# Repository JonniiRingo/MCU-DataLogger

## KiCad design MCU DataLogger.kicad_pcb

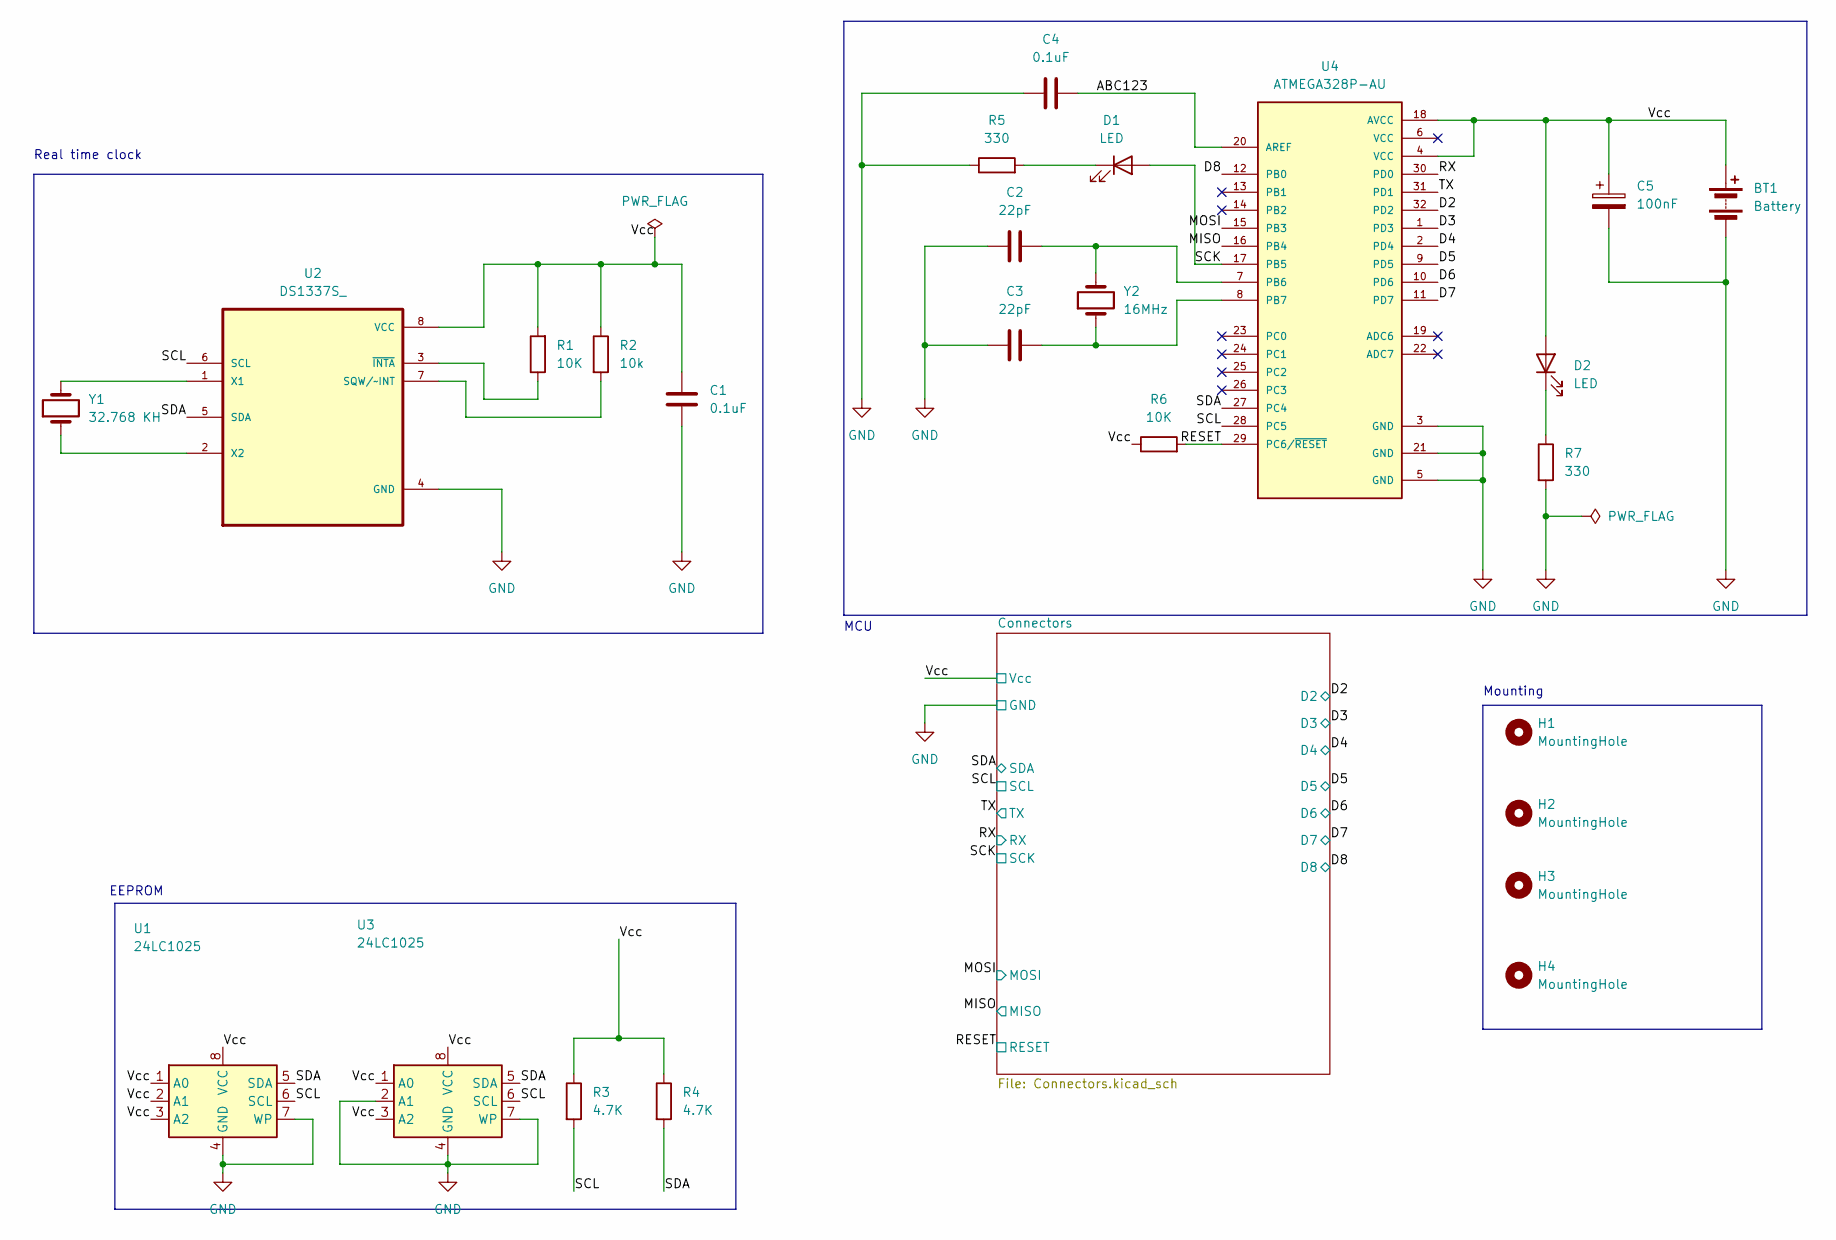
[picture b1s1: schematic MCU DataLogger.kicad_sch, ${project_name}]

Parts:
BT1: Battery; PinHeader_1x02_P2.54mm_Vertical
C1, C4: 0.1uF; C_0805_2012Metric
C2, C3: 22pF; C_0805_2012Metric
C5: 100nF; C_0805_2012Metric
D1, D2: LED; LED_0805_2012Metric
H1, H2, H3, H4: MountingHole; MountingHole_2.1mm
R1, R6: 10K; R_0805_2012Metric
R2: 10k; R_0805_2012Metric
R3, R4: 4.7K; R_0805_2012Metric
R5, R7: 330; R_0805_2012Metric
U1, U3: 24LC1025; SOIC-8_5.3x5.3mm_P1.27mm
U2: DS1337S_; SOIC127P600X175-8N
U4: ATMEGA328P-AU; QFP80P900X900X120-32N; PARTREV 8271A
Y1: 32.768 KH; Crystal_SMD_5032-2Pin_5.0x3.2mm
Y2: 16MHz; Crystal_SMD_5032-2Pin_5.0x3.2mm_HandSoldering

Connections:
/ABC123: C4.2, U4.20 (AREF)
/D2: U4.32 (PD2); also elsewhere on the board
/D3: U4.1 (PD3); also elsewhere on the board
/D4: U4.2 (PD4); also elsewhere on the board
/D5: U4.9 (PD5); also elsewhere on the board
/D6: U4.10 (PD6); also elsewhere on the board
/D7: U4.11 (PD7); also elsewhere on the board
/D8: U4.12 (PB0); also elsewhere on the board
/MISO: U4.16 (PB4); also elsewhere on the board
/MOSI: U4.15 (PB3); also elsewhere on the board
/RESET: R6.2, U4.29 (PC6/~RESET); also elsewhere on the board
/RX: U4.30 (PD0); also elsewhere on the board
/SCK: D1.2 (A), U4.17 (PB5); also elsewhere on the board
/SCL: R3.2, U1.6 (SCL), U2.6 (SCL), U3.6 (SCL), U4.28 (PC5); also elsewhere on the board
/SDA: R4.2, U1.5 (SDA), U2.5 (SDA), U3.5 (SDA), U4.27 (PC4); also elsewhere on the board
/TX: U4.31 (PD1); also elsewhere on the board
/Vcc: BT1.1 (+), C1.2, C5.1, D2.2 (A), R1.2, R2.1, R3.1, R4.1, R6.1, U1.1 (A0), U1.2 (A1), U1.3 (A2), U1.8 (VCC), U2.8 (VCC), U3.1 (A0), U3.3 (A2), U3.8 (VCC), U4.4 (VCC), U4.18 (AVCC); also elsewhere on the board
GND: BT1.2 (-), C1.1, C2.1, C3.1, C4.1, C5.2, R5.1, R7.2, U1.4 (GND), U1.7 (WP), U2.4 (GND), U3.2 (A1), U3.4 (GND), U3.7 (WP), U4.3 (GND), U4.5 (GND), U4.21 (GND); also elsewhere on the board
unnamed: D1.1 (K), R5.2
unnamed: D2.1 (K), R7.1
unnamed: R2.2, U2.7 (SQW/~INT)
unnamed: U2.1 (X1), Y1.2
unnamed: U2.2 (X2), Y1.1
unnamed: R1.1, U2.3 (~INTA)
unnamed: C2.2, U4.7 (PB6), Y2.2
unnamed: C3.2, U4.8 (PB7), Y2.1

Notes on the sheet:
Real time clock
Mounting
MCU
EEPROM

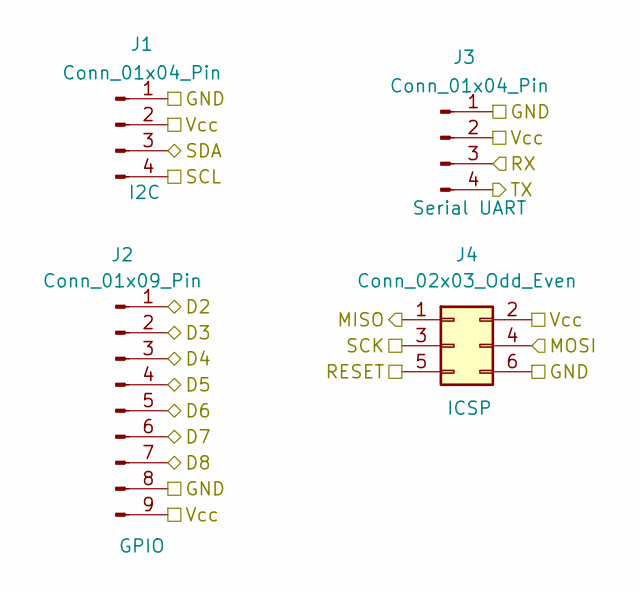
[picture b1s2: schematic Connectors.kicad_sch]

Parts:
J1, J3: Conn_01x04_Pin; PinHeader_1x04_P2.54mm_Vertical
J2: Conn_01x09_Pin; PinHeader_1x09_P2.54mm_Vertical
J4: Conn_02x03_Odd_Even; PinHeader_2x03_P2.54mm_Vertical

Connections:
/D2: J2.1; also elsewhere on the board
/D3: J2.2; also elsewhere on the board
/D4: J2.3; also elsewhere on the board
/D5: J2.4; also elsewhere on the board
/D6: J2.5; also elsewhere on the board
/D7: J2.6; also elsewhere on the board
/D8: J2.7; also elsewhere on the board
/MISO: J4.1; also elsewhere on the board
/MOSI: J4.4; also elsewhere on the board
/RESET: J4.5; also elsewhere on the board
/RX: J3.3; also elsewhere on the board
/SCK: J4.3; also elsewhere on the board
/SCL: J1.4; also elsewhere on the board
/SDA: J1.3; also elsewhere on the board
/TX: J3.4; also elsewhere on the board
/Vcc: J1.2, J2.9, J3.2, J4.2; also elsewhere on the board
GND: J1.1, J2.8, J3.1, J4.6; also elsewhere on the board

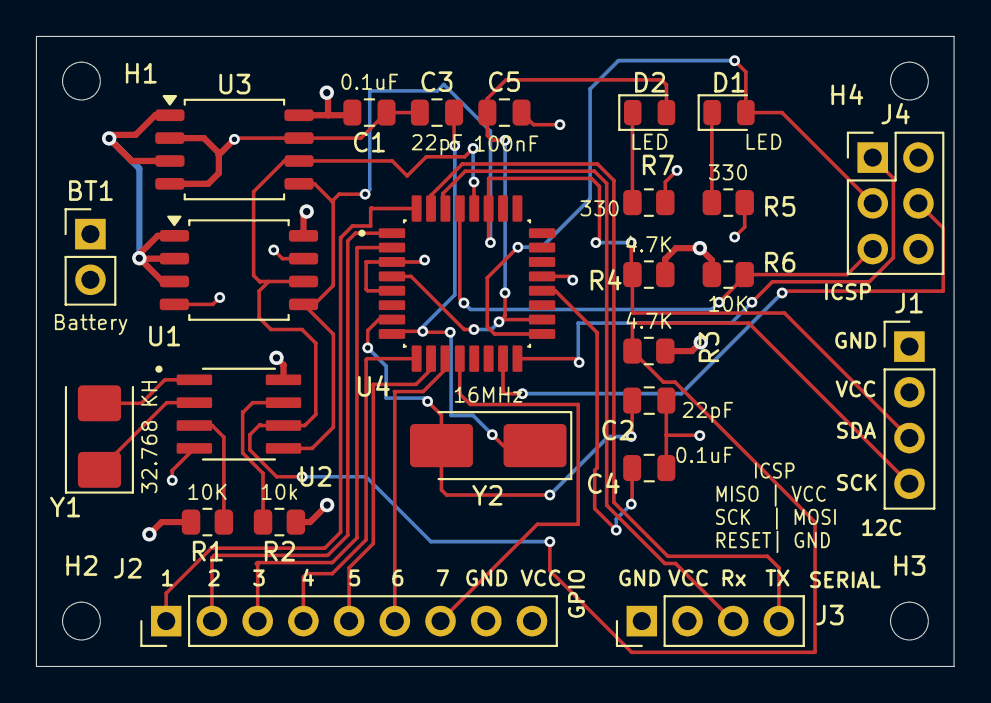
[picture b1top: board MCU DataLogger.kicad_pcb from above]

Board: 4 copper layers, 51.0 x 35.0 mm, 29 parts (0 on the bottom side), 26 nets.

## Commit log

2026-05-12 Settings selected and saved
2026-05-12 Symbols added to first and second sheet
2026-05-12 Symbols arranged pre annonation
2026-05-12 Symbols annotated with componenet values
2026-05-12 Added footprints to most of the symbols
2026-05-12 Sheet one wired
2026-05-12 Both sheets wired but Vcc in sheet 2 is not connected. Maybe some issue with Kicad mismatch
2026-05-13 Trying to resolve unconnected vcc
2026-05-13 Fixed the Erc pin not connected caused by capitalization error VCC vs Vcc
2026-05-13 Added netclass assignments
2026-05-13 Completed the comments on the schematic sheet
2026-05-13 Set up of new pcb with imported netlist
2026-05-13 Added the footprint to U1 and U2, staging for pcb schematic import and layout
2026-05-13 Completed the laout of the footprints in the pcb layer
2026-05-14 Resolved all the unconnected erc errors and assigned the propper cadd model for U2 and U4
2026-05-14 Added copper fill and connected the floating vcc pins and resolved some unconnected GND surface level pins
2026-05-14 Fixed the warnings in the pcb editor from the erc check
2026-05-14 Added labels and callouts to the front layer of the silk screen and reran erc check... 0 warnings one GND pad error (severity 0)
2026-05-14 Added call outs to the silk screen and board charachteristic. Also Exported and inspected the Gerber files. Calculated estimated manufacturing cost to about and shipping
2026-05-14 Renamed the gerber file name
2026-05-14 Updated gerber from 4Layer
2026-05-14 Gerbers staged
2026-05-15 Finalied the 2layer desin moving onto the 4layer routing
2026-05-15 Added the missing RX label for J3 connector
2026-05-16 Finished the 4layer routing
2026-05-16 Staging for the integration of 4layer into main
2026-05-18 Added board charachteristics for 4layer
2026-05-18 added git attributes file
2026-05-18 Made small change to schematic
2026-05-18 Intermediate save before merging update schematic from main
2026-05-19 Staging for schematic bug fixes
2026-05-19 fixed shematic errors SCL vs SCK
2026-05-19 Fixed the routing for the 2layer from updated shematic
2026-05-19 Fixed the SCL vs SCK net list errors routing in the 4layer
